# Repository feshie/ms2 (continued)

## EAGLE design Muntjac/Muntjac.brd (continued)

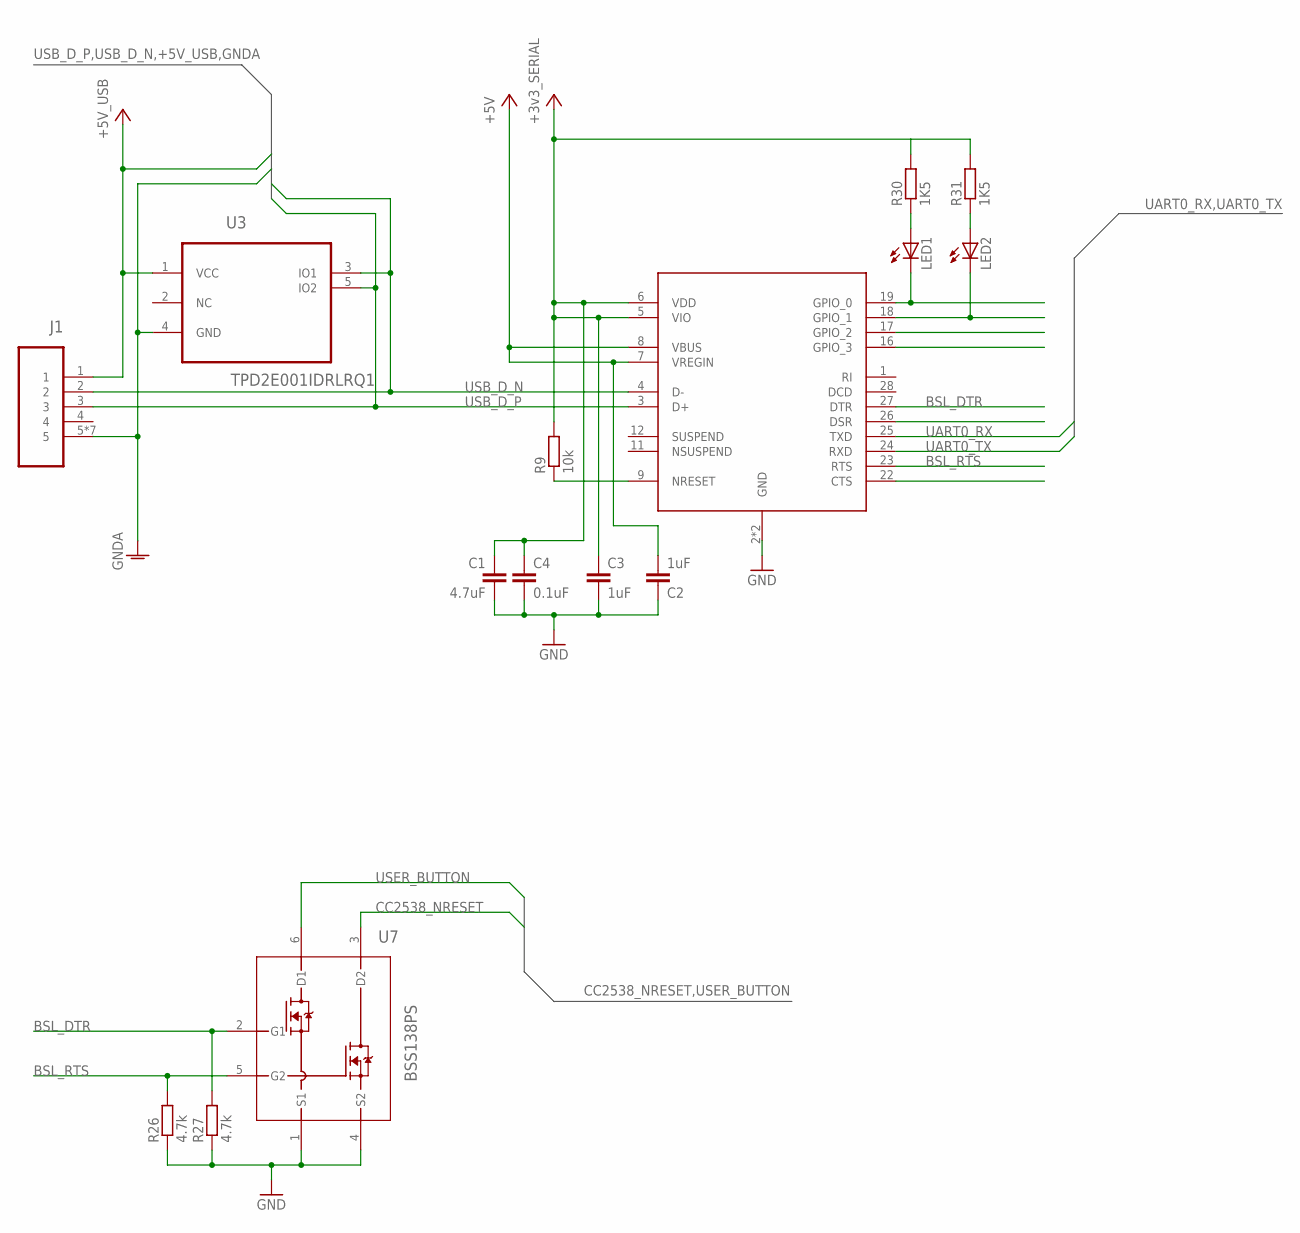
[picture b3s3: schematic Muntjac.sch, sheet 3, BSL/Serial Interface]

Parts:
C1: 4.7uF; C0603
C2, C3: 1uF; C0603
C4: 0.1uF; C0603
J1: 47346-0001; MOLEX_47346-0001
LED1, LED2: LEDSML0603; SML0603
R9: 10k; R0603
R26, R27: 4.7k; R0603
R30, R31: 1K5; R0603
U3: TPD2E001IDRLRQ1; SOT50P160X60-5N
U4: CP2103; QFN50P500X500X100-29N
U7: BSS138PS; SOT65P210X110-6N

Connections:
+3V3_SERIAL: C1.1, C3.1, C4.1, R9.2, R30.2, R31.2, U4.5 (VIO), U4.6 (VDD); also elsewhere on the board
+5V: C2.2, U4.7 (VREGIN), U4.8 (VBUS); also elsewhere on the board
+5V_USB: J1.1, U3.1 (VCC); also elsewhere on the board
BSL_DTR: R27.2, U4.27 (DTR), U7.2 (G1)
BSL_RTS: R26.2, U4.23 (RTS), U7.5 (G2)
CC2538_NRESET: U7.3 (D2); also elsewhere on the board
GND: C1.2, C2.1, C3.2, C4.2, R26.1, R27.1, U4.2 (GND), U4.29 (GND), U7.1 (S1), U7.4 (S2); also elsewhere on the board
GNDA: J1.5, J1.M1 (5), J1.M2 (5), J1.M3 (5), J1.M4 (5), J1.M5 (5), J1.M6 (5), U3.4 (GND); also elsewhere on the board
unnamed: LED1.C, U4.19 (GPIO_0)
unnamed: LED2.C, U4.18 (GPIO_1)
unnamed: LED1.A, R30.1
unnamed: R9.1, U4.9 (NRESET)
unnamed: LED2.A, R31.1
UART0_RX: U4.25 (TXD); also elsewhere on the board
UART0_TX: U4.24 (RXD); also elsewhere on the board
USB_D_N: J1.2, U3.3 (IO1), U4.4 (D-); also elsewhere on the board
USB_D_P: J1.3, U3.5 (IO2), U4.3 (D+); also elsewhere on the board
USER_BUTTON: U7.6 (D1); also elsewhere on the board

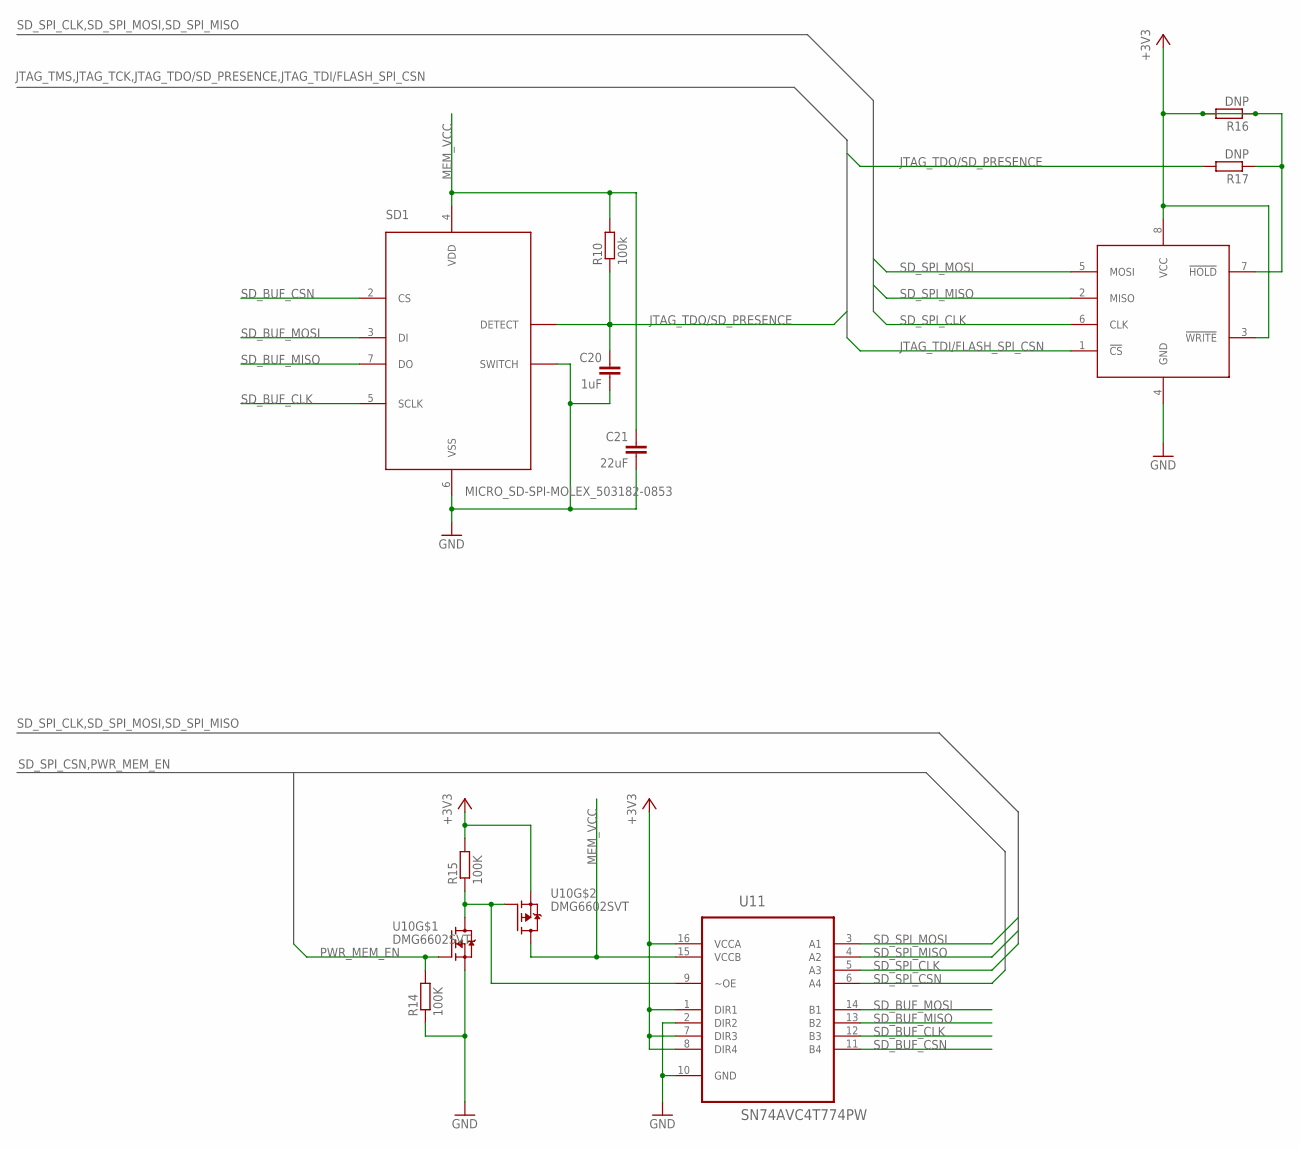
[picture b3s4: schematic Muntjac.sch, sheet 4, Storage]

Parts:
C20: 1uF; C0603
C21: 22uF; C0603
R10: 100k; R0603
R14, R15: 100K; R0603
R16, R17: DNP; R0402
SD1: MICRO_SD-SPI-MOLEX_503182-0853; MICRO_SD-MOLEX_503182-0853
U8: M25P16VMN6P; SOIC8
U10: DMG6602SVT; TSOT26
U11: SN74AVC4T774PW; SOP65P640X120-16N

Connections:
+3V3: R15.2, R16.1, R16.2, R17.1, U8.3 (!WRITE), U8.7 (!HOLD), U8.8 (VCC), U10.P$2 (S), U11.1 (DIR1), U11.7 (DIR3), U11.8 (DIR4), U11.16 (VCCA); also elsewhere on the board
GND: C20.2, C21.2, R14.1, SD1.6 (VSS), SD1.SWITCH, U8.4 (GND), U10.P$5 (S), U11.2 (DIR2), U11.10 (GND); also elsewhere on the board
JTAG_TDI/FLASH_SPI_CSN: U8.1 (!CS); also elsewhere on the board
JTAG_TDO/SD_PRESENCE: C20.1, R10.1, R17.2, SD1.DETECT; also elsewhere on the board
MEM_VCC: C21.1, R10.2, SD1.4 (VDD), U10.P$4 (D), U11.15 (VCCB)
unnamed: R15.1, U10.P$3 (G), U10.P$6 (D), U11.9 (~OE)
PWR_MEM_EN: R14.2, U10.P$1 (G); also elsewhere on the board
SD_BUF_CLK: SD1.5 (SCLK), U11.12 (B3)
SD_BUF_CSN: SD1.2 (CS), U11.11 (B4)
SD_BUF_MISO: SD1.7 (DO), U11.13 (B2)
SD_BUF_MOSI: SD1.3 (DI), U11.14 (B1)
SD_SPI_CLK: U8.6 (CLK), U11.5 (A3); also elsewhere on the board
SD_SPI_CSN: U11.6 (A4); also elsewhere on the board
SD_SPI_MISO: U8.2 (MISO), U11.4 (A2); also elsewhere on the board
SD_SPI_MOSI: U8.5 (MOSI), U11.3 (A1); also elsewhere on the board

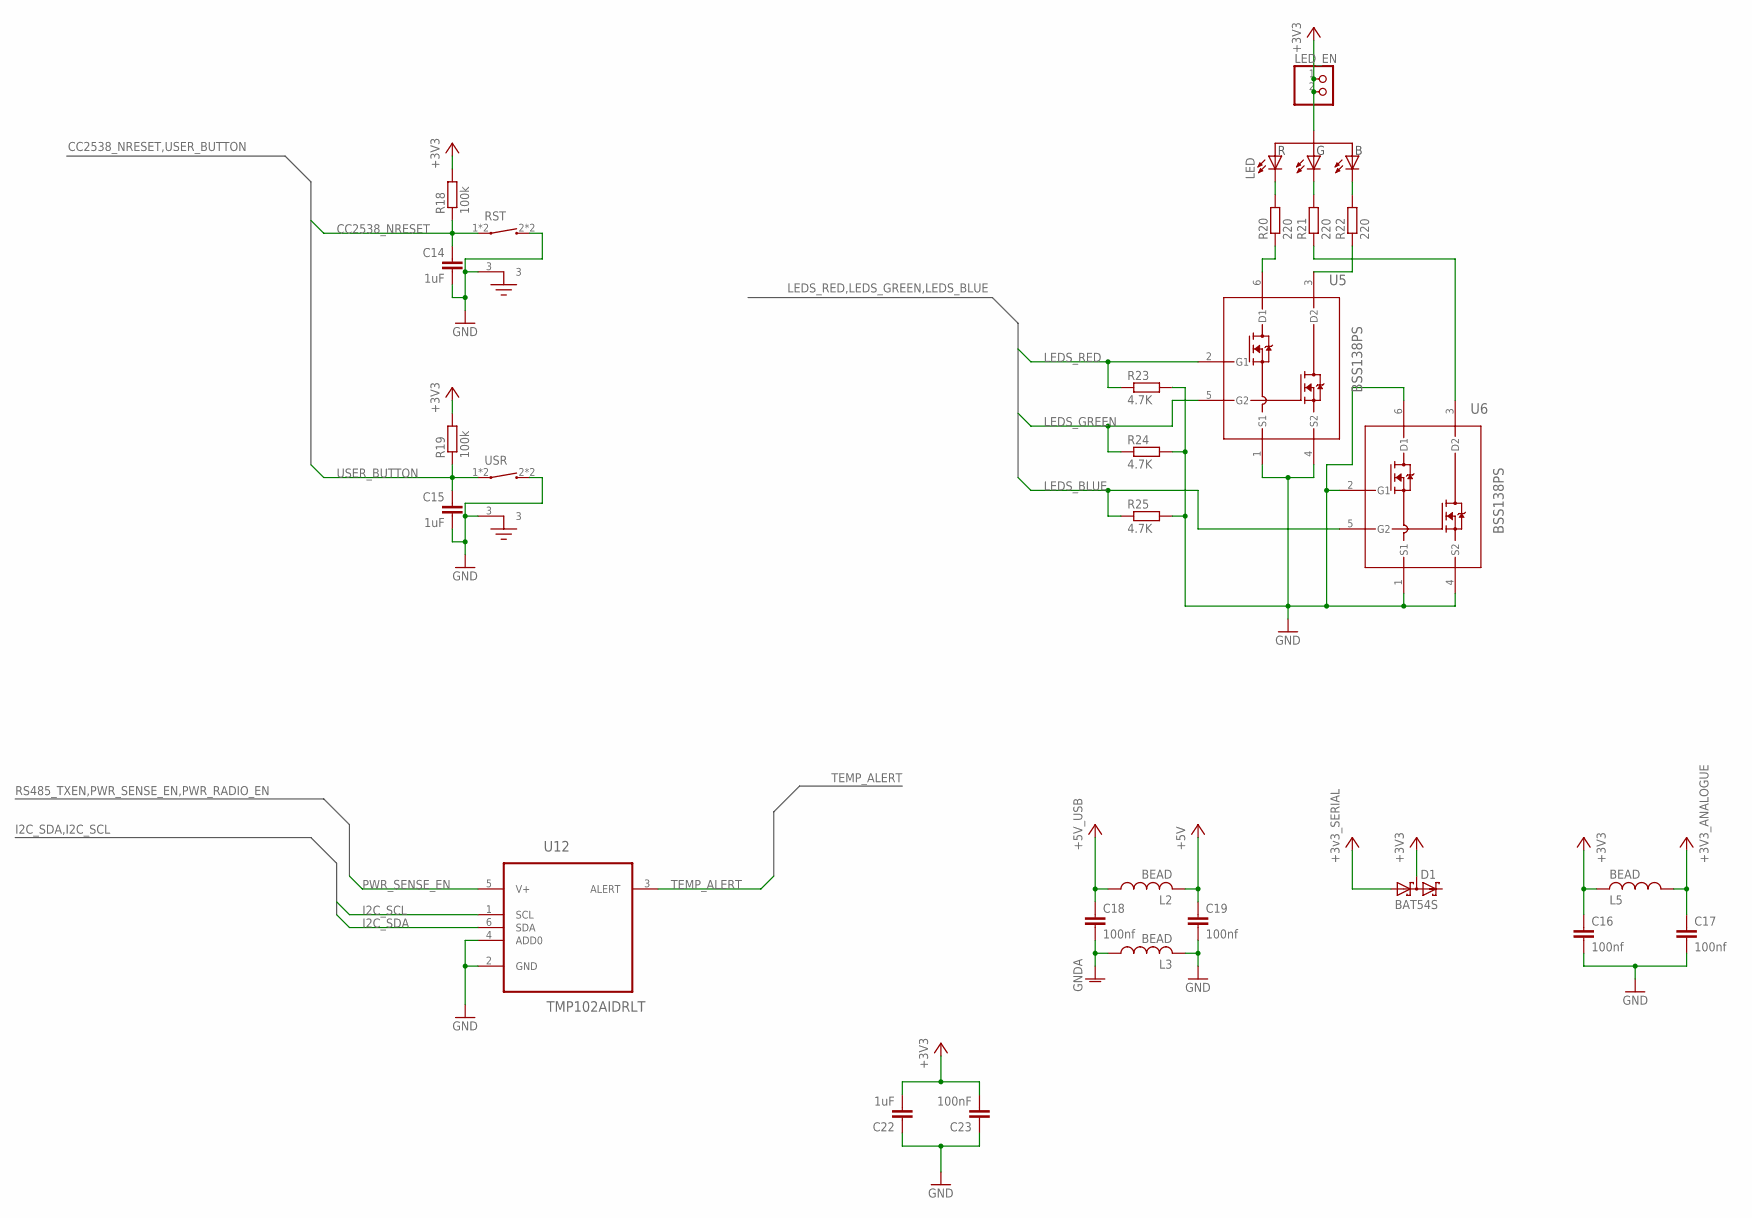
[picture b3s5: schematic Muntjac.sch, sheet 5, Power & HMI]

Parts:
C14, C15, C22: 1uF; C0603
C16, C17, C18, C19: 100nf; C0603
C23: 100nF; C0603
D1: BAT54S; SOT23
L2, L3, L5: BEAD; C0603
LED: CLV1A-FKB-CJ1M1F1BB7R4S3; PLCC-4_3.2X2.8
LED_EN: PINHD-1X2; 1X02
R18, R19: 100k; R0603
R20, R21, R22: 220; R0603
R23, R24, R25: 4.7K; R0603
RST: KMR2X1G; C&K-KMR-5MM
U5, U6: BSS138PS; SOT65P210X110-6N
U12: TMP102AIDRLT; SOT50P160X60-6N
USR: KMR2X1G; C&K-KMR-5MM

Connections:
+3V3: C16.1, C22.2, C23.2, D1.3 (C1A2), L5.2, LED.2, LED_EN.1, LED_EN.2, R18.2, R19.2; also elsewhere on the board
+3V3_ANALOGUE: C17.1, L5.1; also elsewhere on the board
+3V3_SERIAL: D1.1 (A1); also elsewhere on the board
+5V: C19.1, L2.2; also elsewhere on the board
+5V_USB: C18.1, L2.1; also elsewhere on the board
CC2538_NRESET: C14.1, R18.1, RST.1, RST.5 (1); also elsewhere on the board
GND: C14.2, C15.2, C16.2, C17.2, C19.2, C22.1, C23.1, L3.2, R23.2, R24.2, R25.2, RST.2, RST.3, RST.4 (2), U5.1 (S1), U5.4 (S2), U6.1 (S1), U6.2 (G1), U6.4 (S2), U6.6 (D1), U12.2 (GND), U12.4 (ADD0), USR.2, USR.3, USR.4 (2); also elsewhere on the board
GNDA: C18.2, L3.1; also elsewhere on the board
I2C_SCL: U12.1 (SCL); also elsewhere on the board
I2C_SDA: U12.6 (SDA); also elsewhere on the board
LEDS_BLUE: R25.1, U6.5 (G2); also elsewhere on the board
LEDS_GREEN: R24.1, U5.5 (G2); also elsewhere on the board
LEDS_RED: R23.1, U5.2 (G1); also elsewhere on the board
unnamed: LED.1, R20.2
unnamed: LED.3, R21.2
unnamed: LED.4, R22.2
unnamed: R20.1, U5.6 (D1)
unnamed: R21.1, U6.3 (D2)
unnamed: R22.1, U5.3 (D2)
PWR_SENSE_EN: U12.5 (V+); also elsewhere on the board
TEMP_ALERT: U12.3 (ALERT); also elsewhere on the board
USER_BUTTON: C15.1, R19.1, USR.1, USR.5 (1); also elsewhere on the board

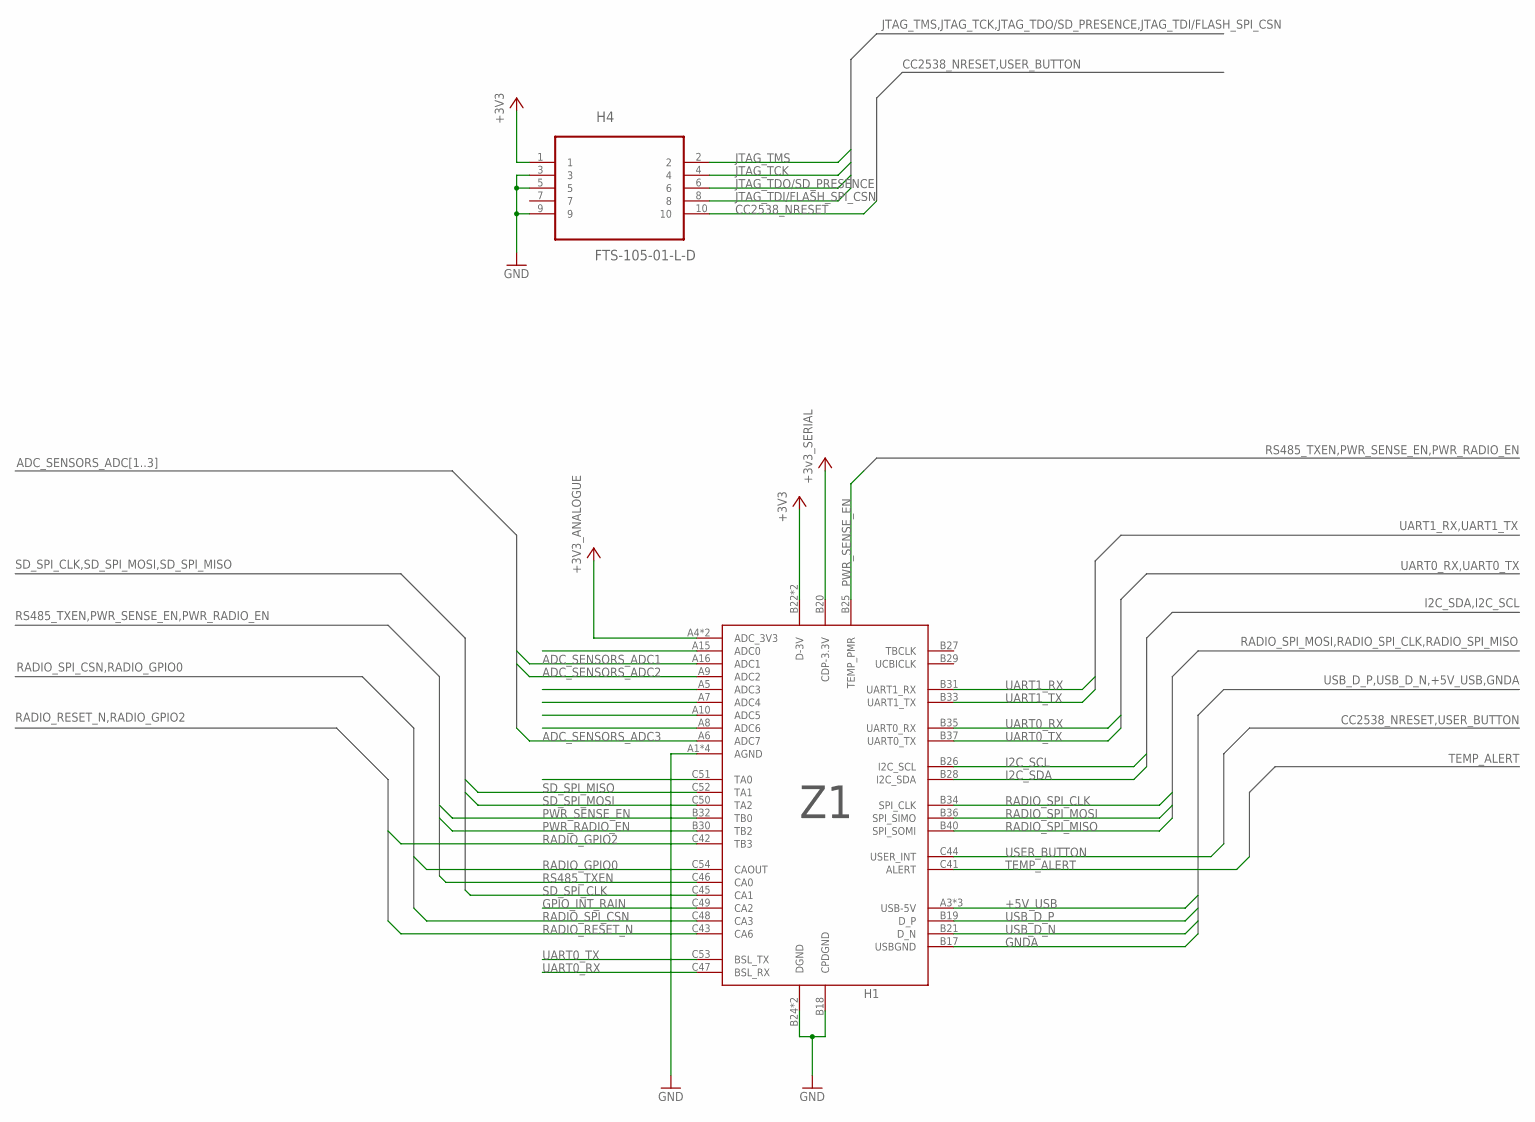
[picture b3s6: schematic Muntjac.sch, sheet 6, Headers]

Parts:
H1: Z1
H4: FTS-105-01-L-D; SAMTEC_FTS-105-01-L-D

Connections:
+3V3: H1.B22 (D-3V), H1.C40 (D-3V), H4.1; also elsewhere on the board
+3V3_ANALOGUE: H1.A4 (ADC_3V3), H1.A14 (ADC_3V3); also elsewhere on the board
+3V3_SERIAL: H1.B20 (CDP-3.3V); also elsewhere on the board
+5V_USB: H1.A3 (USB-5V), H1.A13 (USB-5V), H1.B23 (USB-5V); also elsewhere on the board
ADC_SENSORS_ADC1: H1.A16 (ADC1); also elsewhere on the board
ADC_SENSORS_ADC2: H1.A9 (ADC2); also elsewhere on the board
ADC_SENSORS_ADC3: H1.A6 (ADC7); also elsewhere on the board
CC2538_NRESET: H4.10; also elsewhere on the board
GND: H1.A1 (AGND), H1.A2 (AGND), H1.A11 (AGND), H1.A12 (AGND), H1.B18 (CPDGND), H1.B24 (DGND), H1.C39 (DGND), H4.3, H4.5, H4.9; also elsewhere on the board
GNDA: H1.B17 (USBGND); also elsewhere on the board
GPIO_INT_RAIN: H1.C49 (CA2)
I2C_SCL: H1.B26 (I2C_SCL); also elsewhere on the board
I2C_SDA: H1.B28 (I2C_SDA); also elsewhere on the board
JTAG_TCK: H4.4; also elsewhere on the board
JTAG_TDI/FLASH_SPI_CSN: H4.8; also elsewhere on the board
JTAG_TDO/SD_PRESENCE: H4.6; also elsewhere on the board
JTAG_TMS: H4.2; also elsewhere on the board
PWR_RADIO_EN: H1.B30 (TB2); also elsewhere on the board
PWR_SENSE_EN: H1.B25 (TEMP_PMR), H1.B32 (TB0); also elsewhere on the board
RADIO_GPIO0: H1.C54 (CAOUT); also elsewhere on the board
RADIO_GPIO2: H1.C42 (TB3); also elsewhere on the board
RADIO_RESET_N: H1.C43 (CA6); also elsewhere on the board
RADIO_SPI_CLK: H1.B34 (SPI_CLK); also elsewhere on the board
RADIO_SPI_CSN: H1.C48 (CA3); also elsewhere on the board
RADIO_SPI_MISO: H1.B40 (SPI_SOMI); also elsewhere on the board
RADIO_SPI_MOSI: H1.B36 (SPI_SIMO); also elsewhere on the board
RS485_TXEN: H1.C46 (CA0); also elsewhere on the board
SD_SPI_CLK: H1.C45 (CA1); also elsewhere on the board
SD_SPI_MISO: H1.C52 (TA1); also elsewhere on the board
SD_SPI_MOSI: H1.C50 (TA2); also elsewhere on the board
TEMP_ALERT: H1.C41 (ALERT); also elsewhere on the board
UART0_RX: H1.B35 (UART0_RX), H1.C47 (BSL_RX); also elsewhere on the board
UART0_TX: H1.B37 (UART0_TX), H1.C53 (BSL_TX); also elsewhere on the board
UART1_RX: H1.B31 (UART1_RX); also elsewhere on the board
UART1_TX: H1.B33 (UART1_TX); also elsewhere on the board
USB_D_N: H1.B21 (D_N); also elsewhere on the board
USB_D_P: H1.B19 (D_P); also elsewhere on the board
USER_BUTTON: H1.C44 (USER_INT); also elsewhere on the board

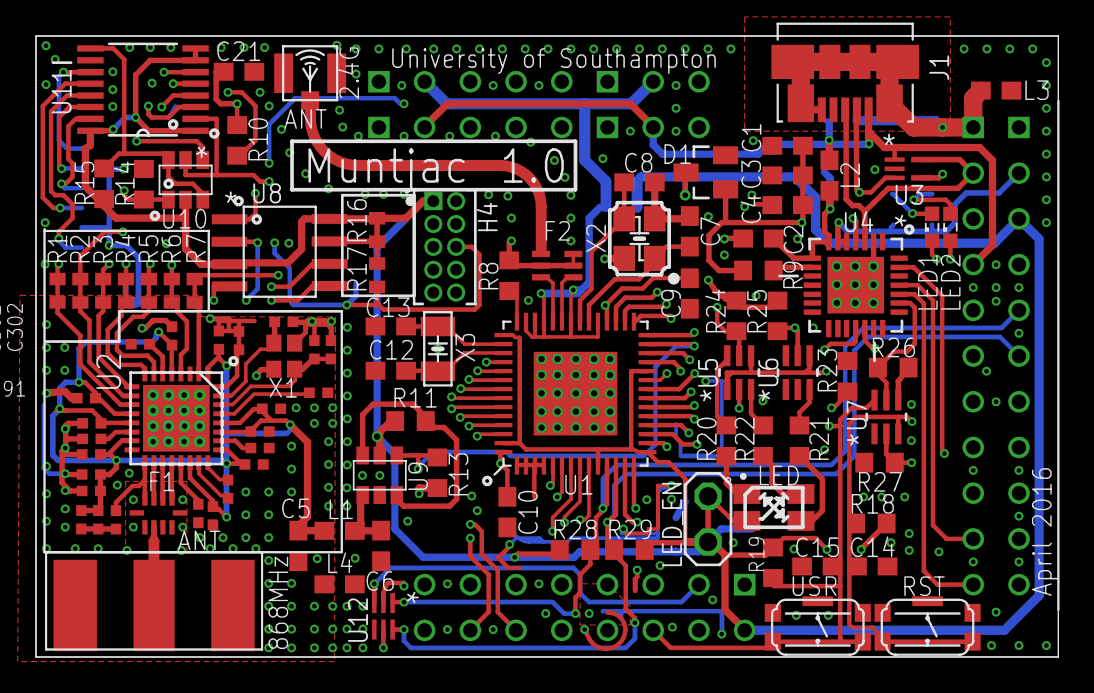
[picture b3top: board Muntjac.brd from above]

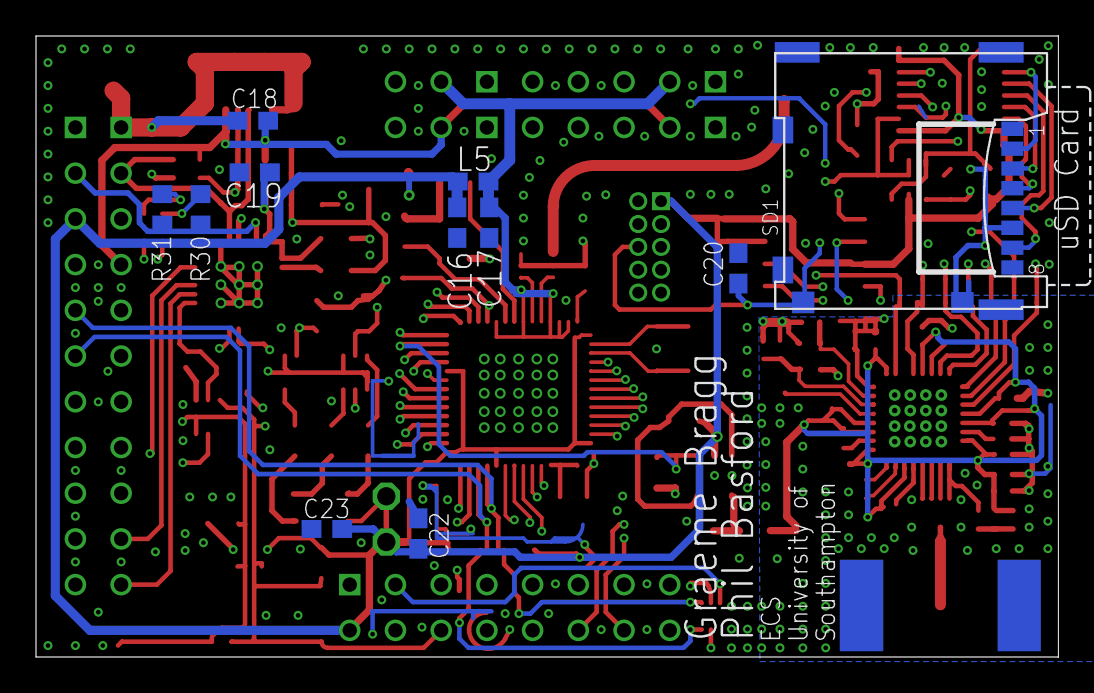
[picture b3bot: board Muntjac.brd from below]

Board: 4 copper layers, 56.8 x 34.5 mm, 111 parts (11 on the bottom side), 90 nets.

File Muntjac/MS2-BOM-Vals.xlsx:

Main Section |  |  | 53
Qty/Brd | Tot | Value | Package | Parts
1 | 3 | USB | USB | J1
2 | 6 | Switch | C&K-KMR-5MM | RST, USR
1 | 3 | UFL | UFL | ANT
1 | 3 | BALUN-2.4G | 2450BM15A0015 | F2
1 | 3 | Tri-colour LED | PLCC-4_3.2X2.8 | LED
1 | 3 | LED Red | 0603 | LED1
1 | 3 | LED Yellow | 0603 | LED2
3 | 9 | 220 | 0603 | R20, R21, R22
2 | 6 | 1K5 | 0603 | R30, R31
3 | 9 | 4.7K | 0603 | R23, R24, R25
3 | 9 | 10k | 0603 | R9, R28, R29
1 | 3 | 56k | 0603 | R8
2 | 6 | 100K | 0603 | R18, R19
4 | 12 | 47p | 0603 | C7, C8, C12, C13
6 | 18 | 100nF | 0603 | C4, C16, C17, C18, C19, C23
7 | 21 | 1uF | 0603 | C2, C3, C9, C10 C14, C15, C22
1 | 3 | 4.7uF | 0603 | C1
1 | 3 | 32.768K | XTAL-3.2X1.5 | X3
1 | 3 | 32MHz | XTAL-3.2X2.5 | X2
3 | 9 | BEAD | 0603 | L2, L3, L5
1 | 3 | BAT54S | SOT23 | D1
1 | 3 | CC2538 | QFN 56 | U1
1 | 3 | TPD2E001IDRLRQ1 | SOT50 | U3
1 | 3 | CP2103 | QFN | U4
2 | 6 | BSS138PS | SOT65 | U5, U6
1 | 3 | M25P16VMN6P | SOIC8 | U8
1 | 3 | TMP102AIDRLT | SOT50 | U12
Through-hole |  |  | 3
Qty/Brd | Tot | Value | Package | Parts
2 | 6 | 2x8 Socket |  | Z1
1 | 3 | 2x11 Socket |  | Z1
Radio Parts |  |  | 33
Qty/Brd | Tot | Value | Package | Parts
1 | 3 | 0900PC15J0013 | Balun/Filter | F1
11 | 33 | 47nF | 0402 | C11, C51, C121, C131, C151, C221, C251, C261, C271, C281, C291
2 | 6 | 15pF | 0402 | C301, C311
1 | 3 | 100pF | 0402 | C172
1 | 3 | 10nH | 0402 | L171
1 | 3 | 220nF | 0402 | C61
1 | 3 | 1.8nF | 0402 | C231
2 | 6 | 10nF | 0402 | C171, C211
1 | 3 | 10R | 0402 | R171
1 | 3 | 33pF | 0402 | C173
1 | 3 | 56K | 0402 | R141
1 | 3 | Crystal | FA-128 | X1 (32MHz for CC1120, 40MHz for CC1200)
1 | 3 | CC1120 | QFN 32 | U2
2 | 6 | BEAD | 0603 | L1, L4
2 | 6 | 100nF | 0603 | C5, C6
2 | 6 | 100K | 0603 | R11, R13
1 | 3 | DMG6602SVT | TSOT26 | U9
1 | 3 | SMA | SMA | ANT_868
SD Card Parts |  |  | 8
Qty/Brd | Tot | Value | Package | Parts
1 | 3 | 1uF | 0603 | C20
1 | 3 | 22uF | 0603 | C21
1 | 3 | MICRO_SD | uSD | SD1
1 | 3 | SN74AVC4T774PW | SOP65 | U11
3 | 9 | 100K | 0603 | R10, R14, R15
1 | 3 | DMG6602SVT | TSOT26 | U10

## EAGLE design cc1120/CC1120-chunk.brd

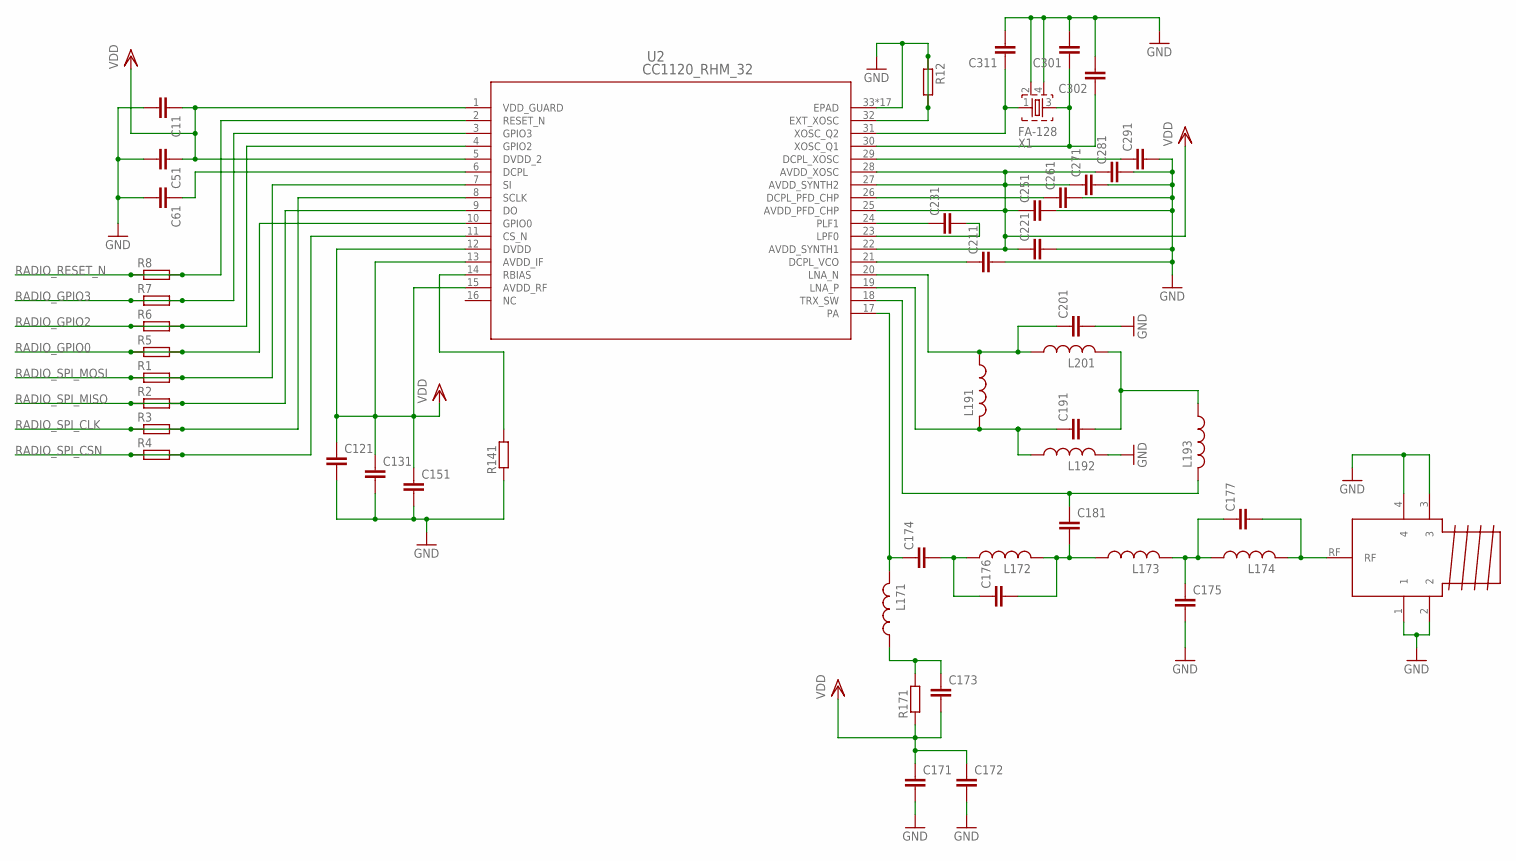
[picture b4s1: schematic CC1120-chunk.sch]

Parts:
ANT_868: SMA; JOHNSON_142-0701-806
C11, C51, C61, C121, C131, C151, C171, C172, C173, C174, C175, C176, C177, C181, C191, C201, C211, C221, C231, C251, C261, C271, C281, C291, C301, C302, C311: C_EU; C0402_SMALL
L171, L172, L173, L174, L191, L192, L193, L201: L_US; C0402_SMALL
R1, R2, R3, R4, R5, R6, R7, R8: R-EU_R0603; R0603
R12, R141, R171: R_EU; C0402_SMALL
U2: CC1120_RHM_32; RHM32_3P7X3P7
X1: FA-128

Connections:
GND: ANT_868.1, ANT_868.2, ANT_868.3, ANT_868.4, C11.2, C51.2, C61.2, C121.2, C131.2, C151.2, C171.2, C172.2, C175.2, C201.2, C211.2, C221.2, C251.2, C261.2, C271.2, C281.2, C291.2, C301.2, C302.2, C311.2, L192.2, R12.1, R12.2, R141.1, U2.32 (EXT_XOSC), U2.33 (EPAD), U2.V (EPAD), U2.V_2 (EPAD), U2.V_3 (EPAD), U2.V_4 (EPAD), U2.V_5 (EPAD), U2.V_6 (EPAD), U2.V_7 (EPAD), U2.V_8 (EPAD), U2.V_9 (EPAD), U2.V_10 (EPAD), U2.V_11 (EPAD), U2.V_12 (EPAD), U2.V_13 (EPAD), U2.V_14 (EPAD), U2.V_15 (EPAD), U2.V_16 (EPAD), X1.2, X1.4
unnamed: C231.1, U2.24 (PLF1)
unnamed: C231.2, U2.23 (LPF0)
unnamed: C211.1, U2.21 (DCPL_VCO)
unnamed: C61.1, U2.6 (DCPL)
unnamed: C261.1, U2.26 (DCPL_PFD_CHP)
unnamed: C311.1, U2.31 (XOSC_Q2), X1.1
unnamed: C301.1, C302.1, U2.30 (XOSC_Q1), X1.3
unnamed: C291.1, U2.29 (DCPL_XOSC)
unnamed: C201.1, L191.1, L201.1, U2.20 (LNA_N)
unnamed: C191.1, L191.2, L192.1, U2.19 (LNA_P)
unnamed: C191.2, L193.1, L201.2
unnamed: C181.1, L193.2, U2.18 (TRX_SW)
unnamed: R141.2, U2.14 (RBIAS)
unnamed: C174.1, L171.2, U2.17 (PA)
unnamed: C174.2, C176.1, L172.1
unnamed: C176.2, C181.2, L172.2, L173.1
unnamed: C175.1, C177.1, L173.2, L174.1
unnamed: ANT_868.RF, C177.2, L174.2
unnamed: C173.1, L171.1, R171.2
RADIO_GPIO0: R5.1, R5.2, U2.10 (GPIO0)
RADIO_GPIO2: R6.1, R6.2, U2.4 (GPIO2)
RADIO_GPIO3: R7.1, R7.2, U2.3 (GPIO3)
RADIO_RESET_N: R8.1, R8.2, U2.2 (RESET_N)
RADIO_SPI_CLK: R3.1, R3.2, U2.8 (SCLK)
RADIO_SPI_CSN: R4.1, R4.2, U2.11 (CS_N)
RADIO_SPI_MISO: R2.1, R2.2, U2.9 (DO)
RADIO_SPI_MOSI: R1.1, R1.2, U2.7 (SI)
VDD: C11.1, C51.1, C121.1, C131.1, C151.1, C171.1, C172.1, C173.2, C221.1, C251.1, C271.1, C281.1, R171.1, U2.1 (VDD_GUARD), U2.5 (DVDD_2), U2.12 (DVDD), U2.13 (AVDD_IF), U2.15 (AVDD_RF), U2.22 (AVDD_SYNTH1), U2.25 (AVDD_PFD_CHP), U2.27 (AVDD_SYNTH2), U2.28 (AVDD_XOSC)

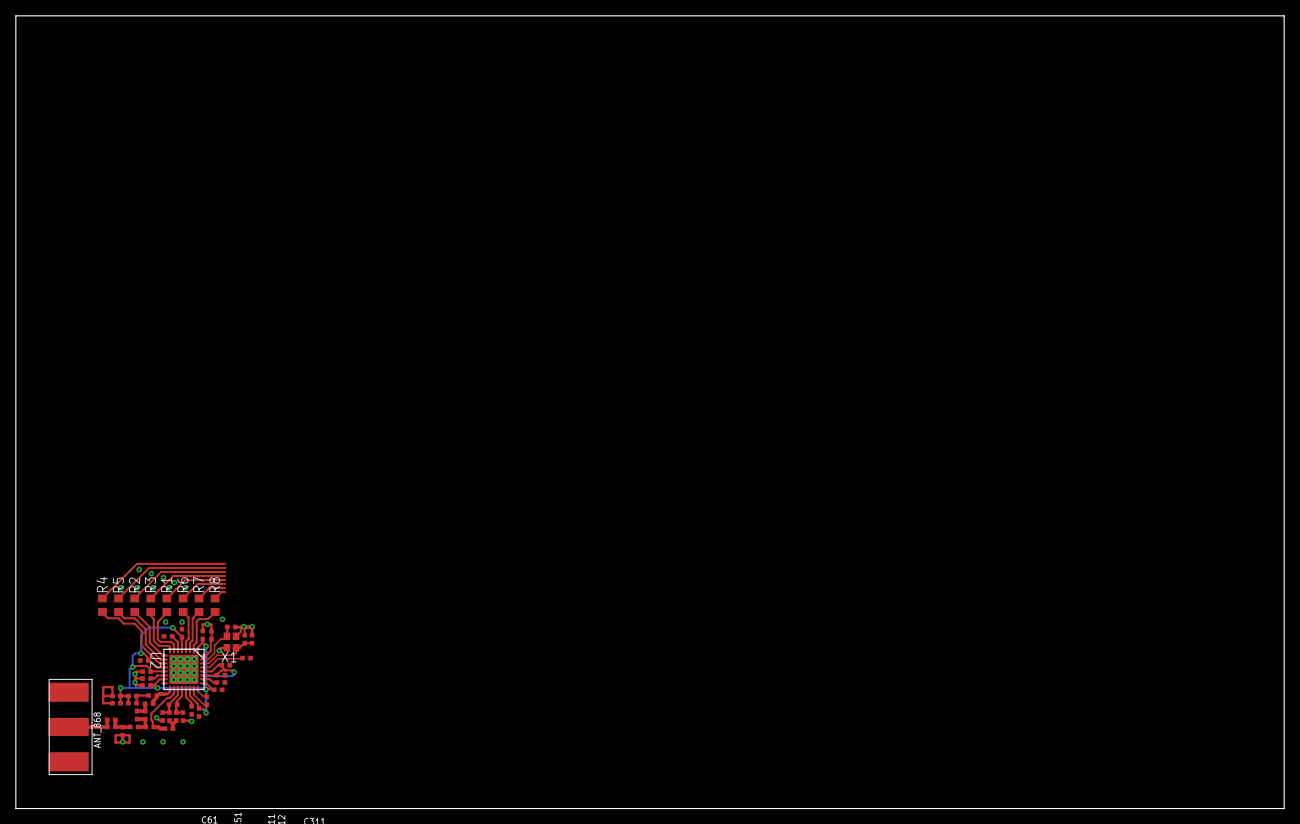
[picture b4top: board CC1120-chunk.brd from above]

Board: 2 copper layers, 160.0 x 100.0 mm, 49 parts (0 on the bottom side), 29 nets.

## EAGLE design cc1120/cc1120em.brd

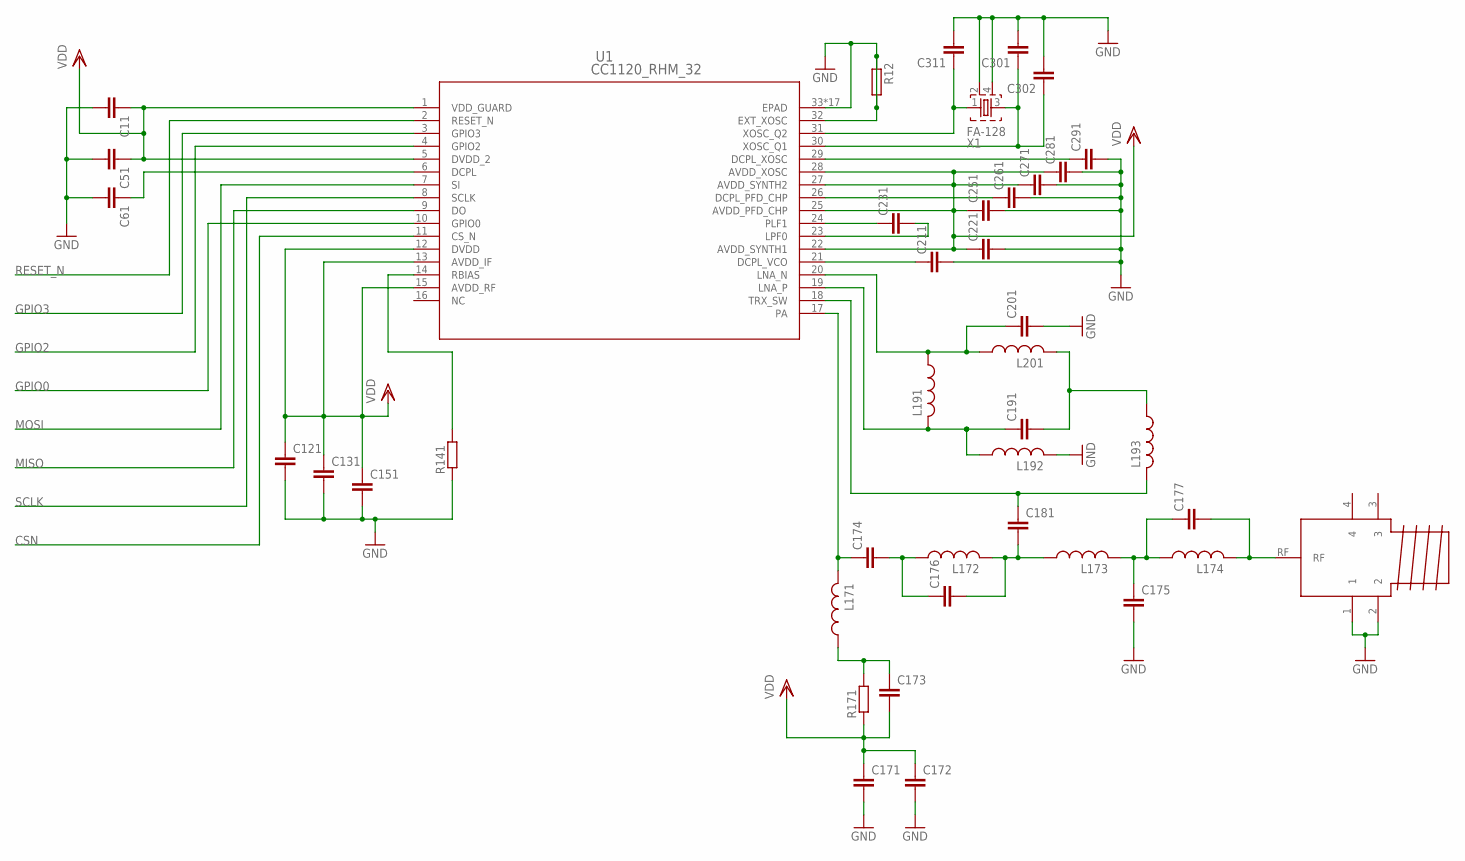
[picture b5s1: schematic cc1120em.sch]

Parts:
ANT_868: SMA; JOHNSON_142-0701-806
C11, C51, C61, C121, C131, C151, C171, C172, C173, C174, C175, C176, C177, C181, C191, C201, C211, C221, C231, C251, C261, C271, C281, C291, C301, C302, C311: C_EU; C0402_SMALL
L171, L172, L173, L174, L191, L192, L193, L201: L_US; C0402_SMALL
R12, R141, R171: R_EU; C0402_SMALL
U1: CC1120_RHM_32; RHM32_3P7X3P7
X1: FA-128

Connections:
3: ANT_868.3
4: ANT_868.4
CSN: U1.11 (CS_N)
GND: ANT_868.1, ANT_868.2, C11.2, C51.2, C61.2, C121.2, C131.2, C151.2, C171.2, C172.2, C175.2, C201.2, C211.2, C221.2, C251.2, C261.2, C271.2, C281.2, C291.2, C301.2, C302.2, C311.2, L192.2, R12.1, R12.2, R141.1, U1.32 (EXT_XOSC), U1.33 (EPAD), U1.V (EPAD), U1.V_2 (EPAD), U1.V_3 (EPAD), U1.V_4 (EPAD), U1.V_5 (EPAD), U1.V_6 (EPAD), U1.V_7 (EPAD), U1.V_8 (EPAD), U1.V_9 (EPAD), U1.V_10 (EPAD), U1.V_11 (EPAD), U1.V_12 (EPAD), U1.V_13 (EPAD), U1.V_14 (EPAD), U1.V_15 (EPAD), U1.V_16 (EPAD), X1.2, X1.4
GPIO0: U1.10 (GPIO0)
GPIO2: U1.4 (GPIO2)
GPIO3: U1.3 (GPIO3)
MISO: U1.9 (DO)
MOSI: U1.7 (SI)
unnamed: C231.1, U1.24 (PLF1)
unnamed: C231.2, U1.23 (LPF0)
unnamed: C211.1, U1.21 (DCPL_VCO)
unnamed: C61.1, U1.6 (DCPL)
unnamed: C261.1, U1.26 (DCPL_PFD_CHP)
unnamed: C311.1, U1.31 (XOSC_Q2), X1.1
unnamed: C301.1, C302.1, U1.30 (XOSC_Q1), X1.3
unnamed: C291.1, U1.29 (DCPL_XOSC)
unnamed: C201.1, L191.1, L201.1, U1.20 (LNA_N)
unnamed: C191.1, L191.2, L192.1, U1.19 (LNA_P)
unnamed: C191.2, L193.1, L201.2
unnamed: C181.1, L193.2, U1.18 (TRX_SW)
unnamed: R141.2, U1.14 (RBIAS)
unnamed: C174.1, L171.2, U1.17 (PA)
unnamed: C174.2, C176.1, L172.1
unnamed: C176.2, C181.2, L172.2, L173.1
unnamed: C175.1, C177.1, L173.2, L174.1
unnamed: ANT_868.RF, C177.2, L174.2
unnamed: C173.1, L171.1, R171.2
RESET_N: U1.2 (RESET_N)
SCLK: U1.8 (SCLK)
VDD: C11.1, C51.1, C121.1, C131.1, C151.1, C171.1, C172.1, C173.2, C221.1, C251.1, C271.1, C281.1, R171.1, U1.1 (VDD_GUARD), U1.5 (DVDD_2), U1.12 (DVDD), U1.13 (AVDD_IF), U1.15 (AVDD_RF), U1.22 (AVDD_SYNTH1), U1.25 (AVDD_PFD_CHP), U1.27 (AVDD_SYNTH2), U1.28 (AVDD_XOSC)

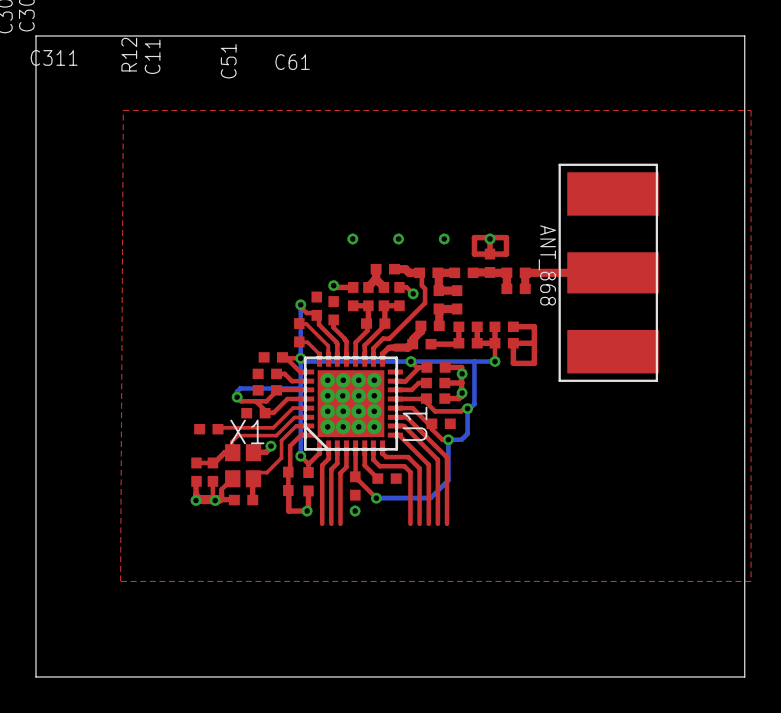
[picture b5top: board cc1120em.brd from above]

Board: 2 copper layers, 39.4 x 35.6 mm, 41 parts (0 on the bottom side), 21 nets.

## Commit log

2016-03-12 First commit of designs for MS2.
    Initial changes to MS1 include removal of RS232 driver and addition of 2x more RS485 driver.
    TODO:
    * Rotate CC1120/1200 footprint
    * Find/design Zoul part
    * Design CC2538 PCB
    * Incorporate MS1 fixes
2016-03-12 CC1120 rotated
2016-03-13 CC1120 ref design first commit
2016-03-14 CC1120 schematic work.
2016-03-15 Work on MS2
2016-03-15 CC1120EM PCB layout
2016-03-15 More work on CC1120 ref design
2016-03-16 Work on CC2538 Z1 board
2016-03-16 renamed a project
2016-03-16 Renamed cc2538 to cc2538-z1
2016-03-16 Work on CC2538 board
2016-03-16 CC2538 design work
2016-03-18 USB input layout done
2016-03-18 Added Radio power filtering & switch.
    I need to stop committing at 6am...
2016-03-26 Board check in before placing & routing CPU
    Added CC1120/1200 ref chunk
    Added partslist with Farnell links
2016-03-27 PCB routing attempt 1
2016-03-27 48 airwires left.
    Still need to finalise SD sel setup.
    May need to swap to a 4-layer board.
    What am I doing working on PCBs at 8 am?
2016-03-28 Last commit before going 4-layer for cc2538 board.
2016-03-30 Moved to a 4-layer board.
    Updated DRU to meet Euro Circuits Class 6C pool service.
    22 airwires left
    TODO: Check SD card SEL implementation.
2016-03-30 A lot of work on 4-layer CC2538/1120 design.
2016-03-31 All traces apart from SDSEL routed. Need to tweak RF layout
2016-03-31 Sorted out the RF traces a bit.
2016-03-31 Added Serial > 3v3 diode.
    Added I2C pullup
    still need to work out SD SEL
2016-04-01 Added 2-pin round pinhead
2016-04-01 plit schematic into separate pages & added framesy
2016-04-01 Added SPI Flash & moved 2.4G UFL
2016-04-05 Routing finished? need to sanity check.
    Check pull ups for SPI
2016-04-06 Added level translator for SPI power down, resized some DNP resistors, some other minor changes.
2016-04-08 Finalised board design?
2016-04-08 Renamed PCB to Muntjac
2016-04-09 Added LEDs for Serial TX/RX.
    brd as submitted for manufacture.
2016-04-13 Final Muntjac 1.0 commit for manufacture
2016-04-16 Added values to schematic for CC1120 layout.
    Updated parts list.
2016-06-03 Added LTSpice schematic of Switch mode + LDO combo.
    Work on MS2.
2016-06-06 "new" power supply implemented on ms2
    Added Eagle files for CC1120 breakout.
2016-06-08 More MS2 layout work.
2016-06-08 More MS2 layout work. 23 remaining airwires.
2016-06-14 MS2 as submitted for manufacture
2016-07-04 Added Pick & Place BOM plus table feed layout
2016-07-05 Finished Pick & Place layout.
2016-07-06 Added MS2 SMD Part holder schematic for use with laser cutter
2016-07-06 Corrections to MS2 pick & place layout.
2016-07-06 Typo fix in Pick & Place layout
2016-07-07 Muntjac hand/Pick&Place layout + component trays.
2016-07-07 Added Muntjac Solderpaste layer
